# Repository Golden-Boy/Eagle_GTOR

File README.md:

# Eagle_GTOR
Custom PCB For Inertial Measurement Unit (IMU)

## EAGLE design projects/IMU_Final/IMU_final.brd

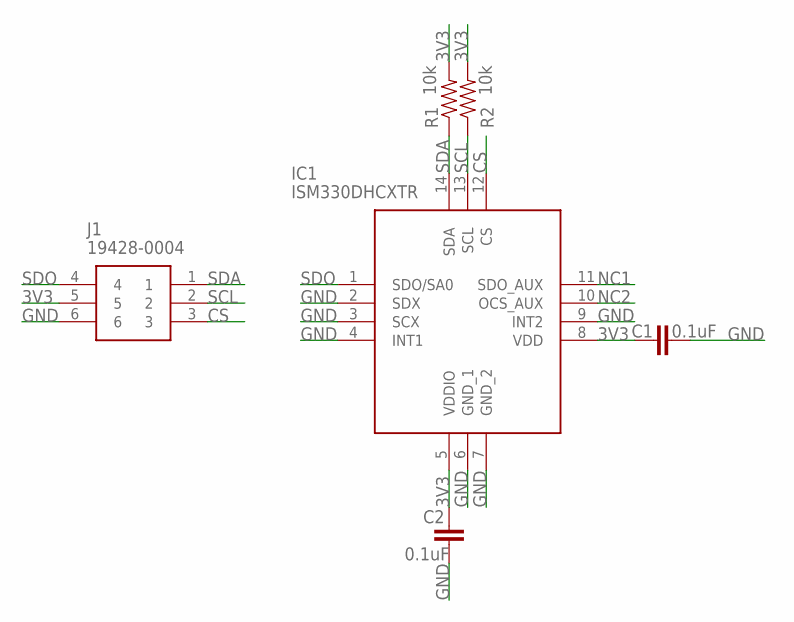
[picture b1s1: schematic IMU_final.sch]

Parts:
C1, C2: 0.1uF; 0603
IC1: ISM330DHCXTR; LGA-14(2.5X3X0.86)
J1: 19428-0004; 194280004
R1, R2: 10k; 0603

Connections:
3V3: C1.1, C2.1, IC1.5 (VDDIO), IC1.8 (VDD), J1.5, R1.2, R2.2
CS: IC1.12 (CS), J1.3
GND: C1.2, C2.2, IC1.2 (SDX), IC1.3 (SCX), IC1.4 (INT1), IC1.6 (GND_1), IC1.7 (GND_2), IC1.9 (INT2), J1.6
NC1: IC1.11 (SDO_AUX)
NC2: IC1.10 (OCS_AUX)
SCL: IC1.13 (SCL), J1.2, R2.1
SDA: IC1.14 (SDA), J1.1, R1.1
SDO: IC1.1 (SDO/SA0), J1.4

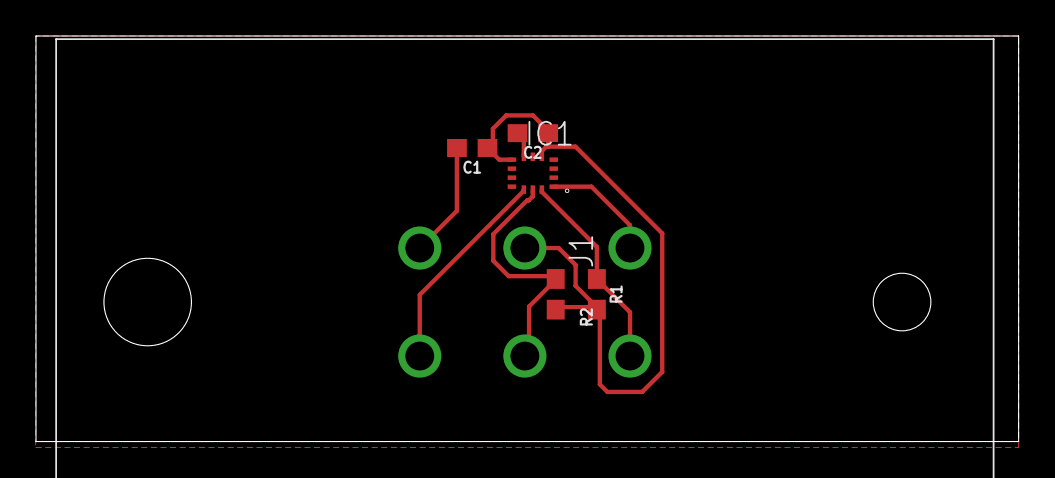
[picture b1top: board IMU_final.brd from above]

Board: 2 copper layers, 54.6 x 22.5 mm, 6 parts (0 on the bottom side), 6 nets.

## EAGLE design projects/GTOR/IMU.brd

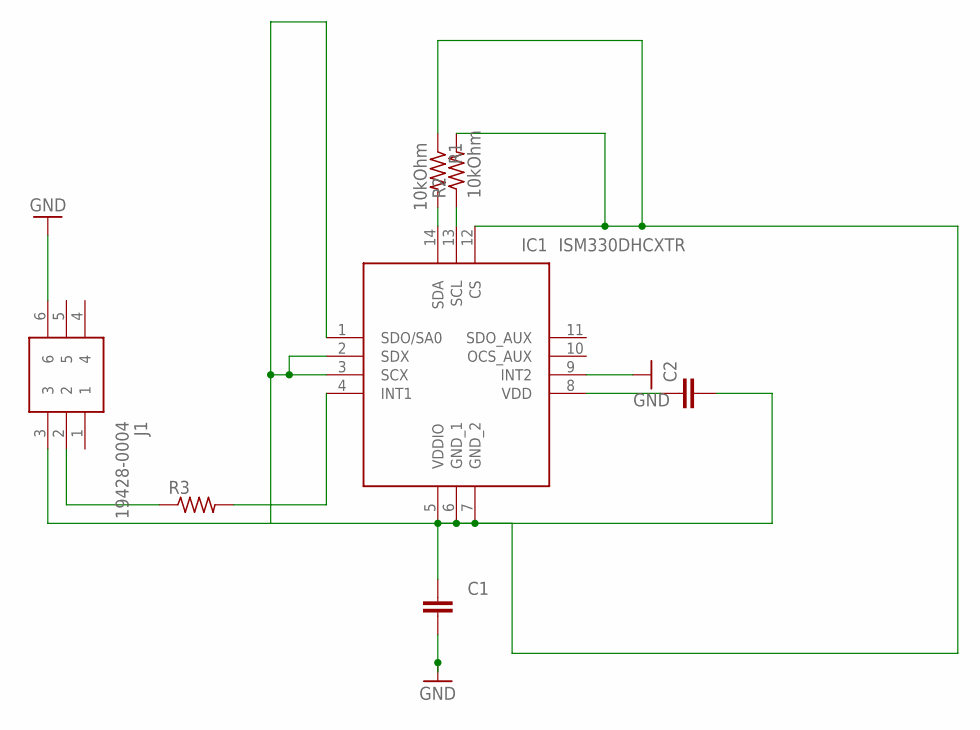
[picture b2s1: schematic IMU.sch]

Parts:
C1, C2: C-EUC0805; C0805
IC1: ISM330DHCXTR; LGA-14(2.5X3X0.86)
J1: 19428-0004; 194280004
R1, R2: 10kOhm; 0411/12
R3: R-US_R0805; R0805

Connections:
GND: C1.2, IC1.9 (INT2), J1.6
unnamed: IC1.1 (SDO/SA0), IC1.2 (SDX), IC1.3 (SCX)
unnamed: C1.1, C2.2, IC1.5 (VDDIO), IC1.6 (GND_1), IC1.7 (GND_2), IC1.12 (CS), J1.3, R1.1, R2.2
unnamed: IC1.13 (SCL), R2.1
unnamed: C2.1, IC1.8 (VDD)
unnamed: IC1.14 (SDA), R1.2
unnamed: J1.2, R3.1
unnamed: IC1.4 (INT1), R3.2

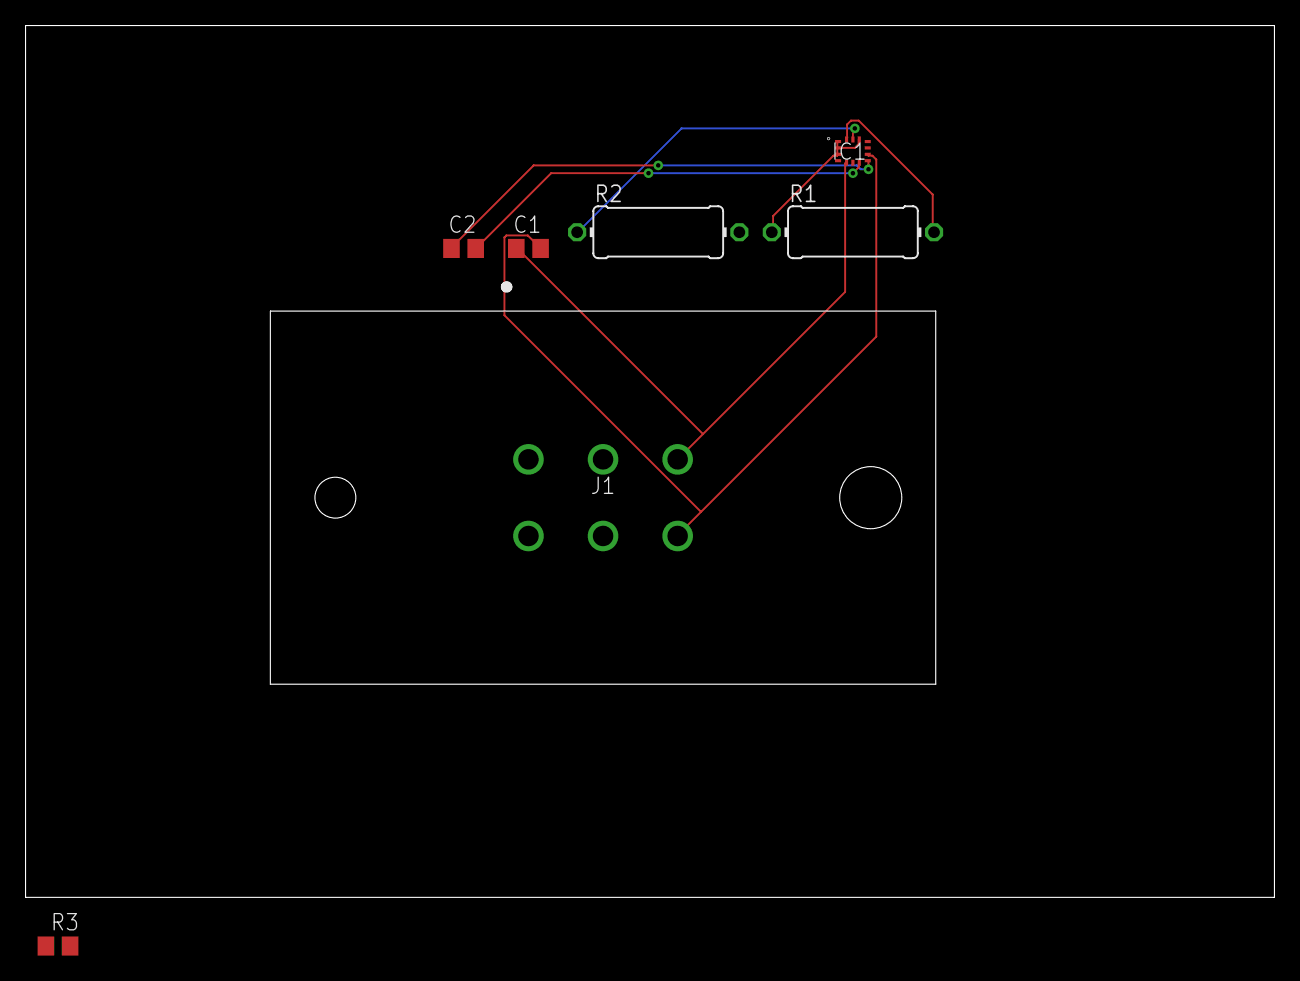
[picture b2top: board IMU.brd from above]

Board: 2 copper layers, 97.8 x 68.2 mm, 7 parts (0 on the bottom side), 8 nets.

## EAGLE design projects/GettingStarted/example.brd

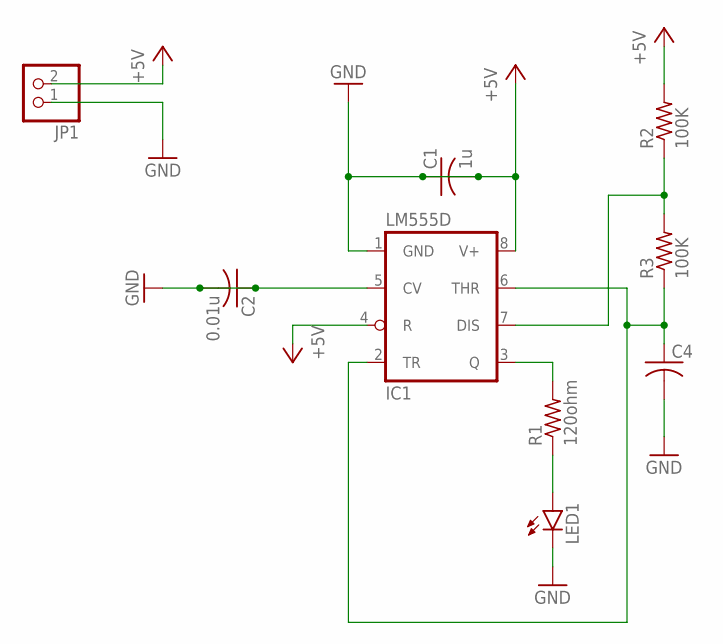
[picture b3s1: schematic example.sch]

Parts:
C1: 1u; C0805
C2: 0.01u; C0805
C4: C-USC0805; C0805
IC1: LM555D; SO08
JP1: PINHD-1X2; 1X02
LED1: LED5MM
R1: 120ohm; M0805
R2, R3: 100K; M0805

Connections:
+5V: C1.1, C1.2, IC1.1 (GND), IC1.4 (R), IC1.8 (V+), JP1.2, R2.2
GND: C2.1, C2.2, C4.2, IC1.5 (CV), JP1.1, LED1.K (C)
unnamed: IC1.7 (DIS), R2.1, R3.2
unnamed: IC1.3 (Q), R1.2
unnamed: LED1.A, R1.1
unnamed: C4.1, IC1.2 (TR), IC1.6 (THR), R3.1

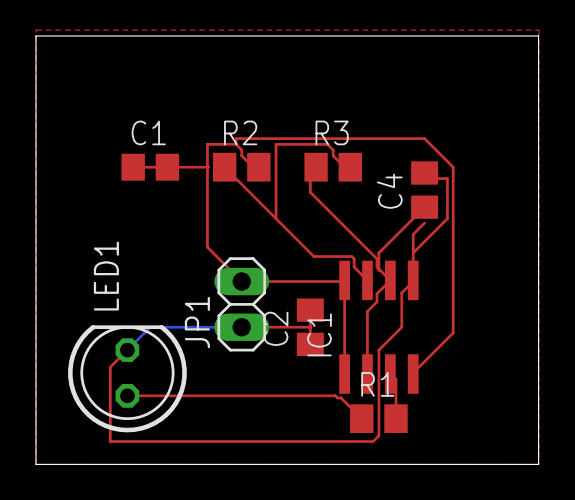
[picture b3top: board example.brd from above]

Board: 2 copper layers, 27.9 x 23.8 mm, 9 parts (0 on the bottom side), 6 nets.

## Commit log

2020-06-11 Design Change 1
2020-06-12 Added chip select pin
2020-06-20 added pin header
2020-06-27 Complete IMU Schematic
2020-06-27 Final IMU Schematic

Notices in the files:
parts and their libraries:
SparkFun-Capacitors: Licensing: Creative Commons ShareAlike 4.0 International - https://creativecommons.org/licenses/by-sa/4.0
